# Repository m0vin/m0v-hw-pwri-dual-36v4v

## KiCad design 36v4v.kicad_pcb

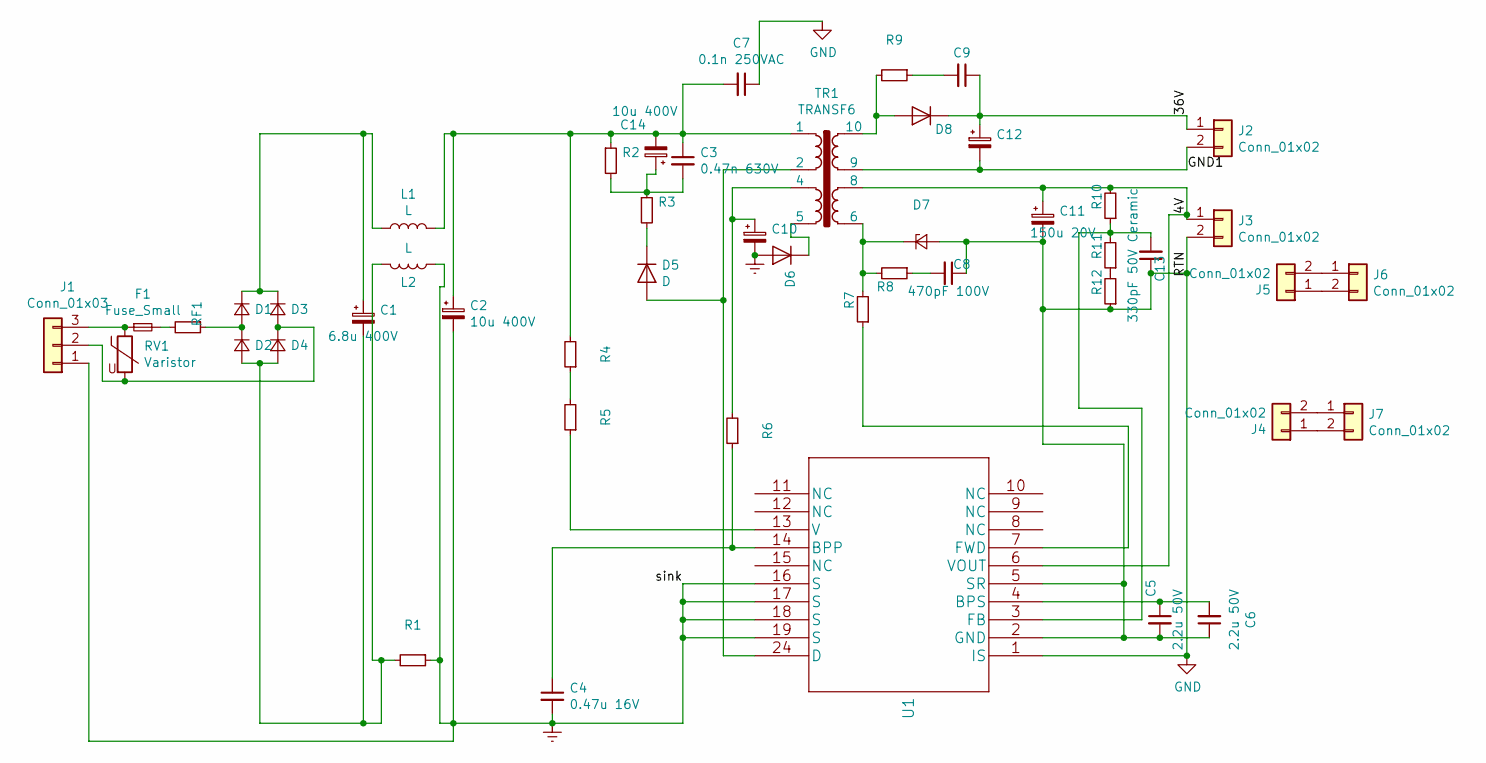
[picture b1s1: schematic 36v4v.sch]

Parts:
C1: 6.8u 400V; CP_Radial_D10.0mm_P5.00mm; MFG Part Num ESH106M450AH4AA/EEV-EB2G100SM
C2, C14: 10u 400V; CP_Radial_D10.0mm_P5.00mm; MFG Part Num ESH106M450AH4AA/EEV-EB2G100SM
C3: 0.47n 630V; CP_Radial_Tantal_D5.5mm_P5.00mm; MFG Part Num RCE7U2J471J2M1H03A
C4: 0.47u 16V; C_0603_1608Metric_Pad1.05x0.95mm_HandSolder; MFG Part Num GRM033R71E471KA01D/FK18X7R1C474K
C5, C6: 2.2u 50V; C_0603_1608Metric_Pad1.05x0.95mm_HandSolder; MFG Part Num GRM188R61H225KE11D/C340C225K5R5TA
C7: 0.1n 250VAC; C_Disc_D8.0mm_W5.0mm_P10.00mm; MFG Part Num 440LT10-R
C8: 470pF 100V; C_0603_1608Metric_Pad1.05x0.95mm_HandSolder; MFG Part Num 885342006005/K471J15C0GH5TH5
C9: 18pF 1KV Ceramic; CP_Radial_D10.0mm_P5.00mm; MFG Part Num ECC-D3A180JGE
C10: 22u 35V Electrolytic; CP_Radial_D5.0mm_P2.00mm; MFG Part Num 860020672011/EEU-FC1V220H
C11: 150u 20V; CP_Radial_D10.0mm_P5.00mm; MFG Part Num PLF1D151MDO2TD/860010674014
C12: 22u 50V Electrolytic; CP_Radial_D5.0mm_P2.00mm; MFG Part Num 860020672011/EKZE500ELL220ME11D
C13: 330pF 50V Ceramic; C_0603_1608Metric_Pad1.05x0.95mm_HandSolder; MFG Part Num 885342006005/K471J15C0GH5TH5
D1, D2, D3, D4: D_Small; D_SMB_Handsoldering; MFG Part Num VS-4EGU06-M3/5BT OR GBL06-E3/45GI-ND OR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
D5: D; D_SMA_Handsoldering; MFG Part Num US1M
D6: 150 V, 0.2 A, Standard Recovery, DO-35; D_SMA_Handsoldering; MFG Part Num US1M/1N3595TR
D7: 40 V, 2 A, Schottky, DO-15; D_SMA_Handsoldering; MFG Part Num B240A-E3/61T OR SB240-E3/54
D8: 400 V, 1 A, Ultrafast Recovery, 30 ns, SOD57; D_SMA_Handsoldering; MFG Part Num US1M/BYV26B-TR
F1: Fuse_Small; Fuseholder_Cylinder-5x20mm_Schurter_0031_8201_Horizontal_Op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
J1: Conn_01x03; PhoenixContact_MCV_1,5_3-G-5.08_1x03_P5.08mm_Vertical
J2, J3, J6, J7: Conn_01x02; PinHeader_1x02_P2.54mm_Vertical
J4, J5: Conn_01x02; SolderWirePad_1x02_P5.08mm_Drill1.5mm
L1, L2: L; L_Radial_D6.0mm_P4.00mm; MFG Part Num SBC2-102-181
R1: 4.7 kΩ, 5 %, 0.25 W, Carbon Film; R_0805_2012Metric_Pad1.15x1.40mm_HandSolder
R2: 240 kΩ, 5 %, 0.25 W, Carbon Film; R_2512_6332Metric_Pad1.52x3.35mm_HandSolder
R3: 43 Ω, 5 %, 0.125 W, Carbon Film; R_0805_2012Metric_Pad1.15x1.40mm_HandSolder
R4, R5: 1.78 MΩ, 1 %, 0.25 W, Metal Film; R_0805_2012Metric_Pad1.15x1.40mm_HandSolder
R6: 14 kΩ, 1 %, 0.125 W, Metal Film; R_0805_2012Metric_Pad1.15x1.40mm_HandSolder
R7: 47 Ω, 5 %, 0.125 W, Carbon Film; R_0603_1608Metric_Pad1.05x0.95mm_HandSolder
R8: 22 Ω, 5 %, 0.25 W, Carbon Film; R_0603_1608Metric_Pad1.05x0.95mm_HandSolder
R9: 560 Ω, 5 %, 0.25 W, Carbon Film; R_0603_1608Metric_Pad1.05x0.95mm_HandSolder
R10: 80.6 kΩ, 1 %, 0.125 W, Metal Film; R_0603_1608Metric_Pad1.05x0.95mm_HandSolder
R11, R12: 29.4 kΩ, 1 %, 0.125 W, Metal Film; R_0603_1608Metric_Pad1.05x0.95mm_HandSolder
RF1: 10 Ω, 2 W, Flameproof Wire-Wound Resistor; R_2816_7142Metric; MFG Part Num SMW210RJT
RV1: Varistor; RV_Disc_D7mm_W4mm_P5mm
TR1: TRANSF6; xformer_2xPri_2xSec
U1: InnoSwitch3-CE, INN3162C, inSOP-24D; INN3162C-H1XX_; MFG Part Num INN3162C-H101

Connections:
/4V: C11.1, J3.1, R10.2, TR1.8, U1.6 (VOUT)
/36V: C9.1, C12.1, D8.1 (K), J2.1
/GND1: C12.2, J2.2, TR1.9
Earth: C2.2, C4.2, C10.2, D6.2 (A), J1.1, L2.1, R1.1, U1.16 (S), U1.17 (S), U1.18 (S), U1.19 (S)
GND: C5.2, C6.1, C7.1, C8.1, C11.2, C13.1, D7.2 (A), J3.2, R12.1, U1.1 (IS), U1.2 (GND), U1.5 (SR)
unnamed: C1.1, D1.1 (K), D3.1 (K), L1.1
unnamed: C1.2, D2.2 (A), D4.2 (A), L2.2, R1.2
unnamed: C4.1, R6.1, U1.14 (BPP)
unnamed: C5.1, C6.2, U1.4 (BPS)
unnamed: C8.2, R8.1
unnamed: C9.2, R9.1
unnamed: C10.1, R6.2, TR1.4
unnamed: C13.2, R10.1, R11.2, U1.3 (FB)
unnamed: C3.2, C14.1, R2.2, R3.1
unnamed: C2.1, C3.1, C7.2, C14.2, L1.2, R2.1, R4.2, TR1.1
unnamed: D1.2 (A), D2.1 (K), RF1.1
unnamed: D3.2 (A), D4.1 (K), J1.2, RV1.2
unnamed: D5.1 (K), R3.2
unnamed: D5.2 (A), TR1.2, U1.24 (D)
unnamed: D6.1 (K), TR1.5
unnamed: D7.1 (K), R7.2, R8.2, TR1.6
unnamed: D8.2 (A), R9.2, TR1.10
unnamed: F1.1, J1.3, RV1.1
unnamed: F1.2, RF1.2
unnamed: J4.1, J7.2
unnamed: J4.2, J7.1
unnamed: J5.1, J6.2
unnamed: J5.2, J6.1
unnamed: R4.1, R5.2
unnamed: R5.1, U1.13 (V)
unnamed: R7.1, U1.7 (FWD)
unnamed: R11.1, R12.2

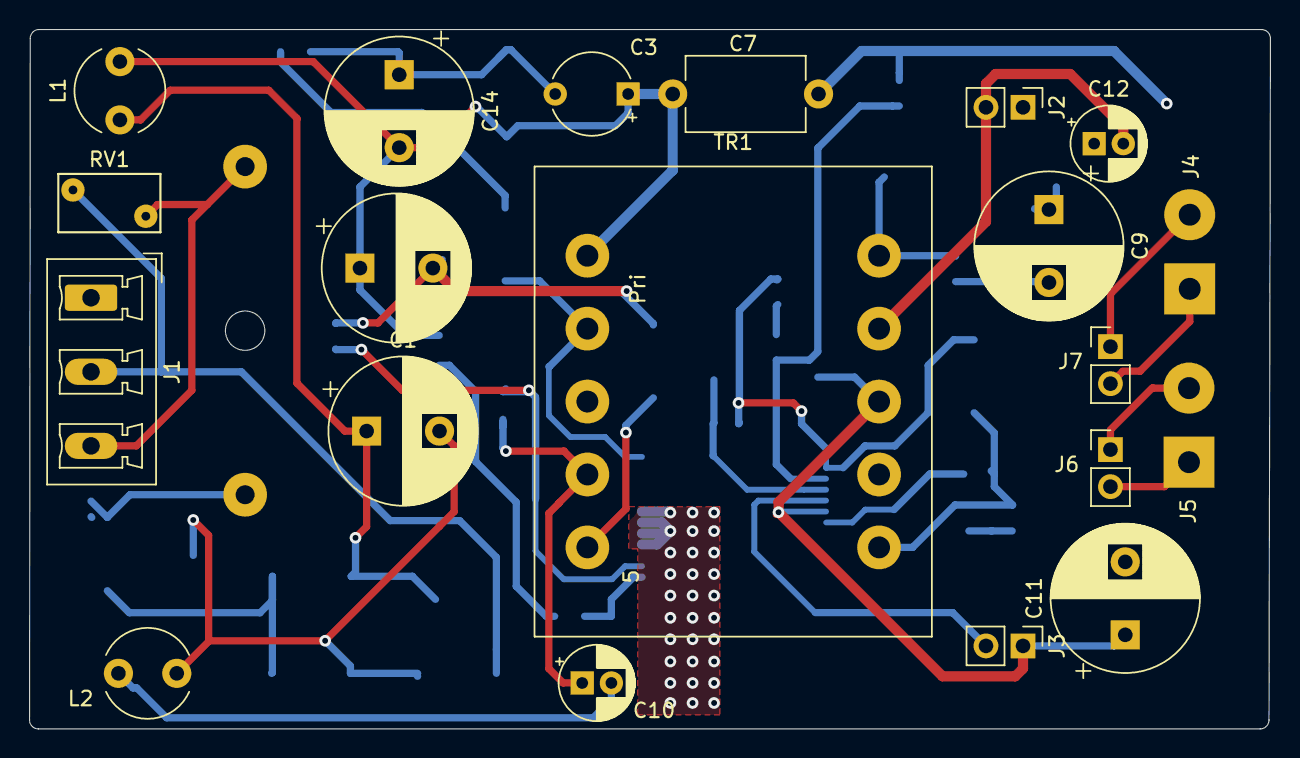
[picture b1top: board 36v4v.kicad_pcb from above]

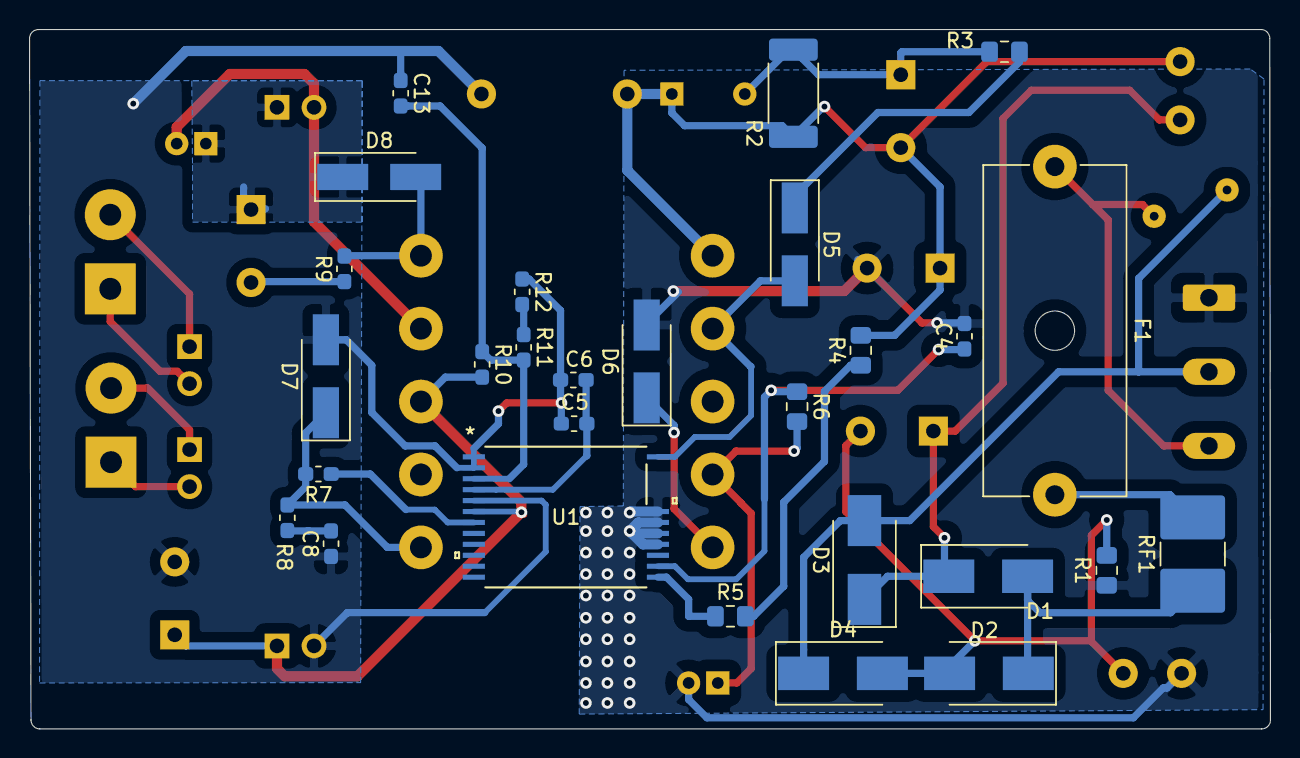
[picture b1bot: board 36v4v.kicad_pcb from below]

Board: 2 copper layers, 85.1 x 48.0 mm, 48 parts (28 on the bottom side), 32 nets.

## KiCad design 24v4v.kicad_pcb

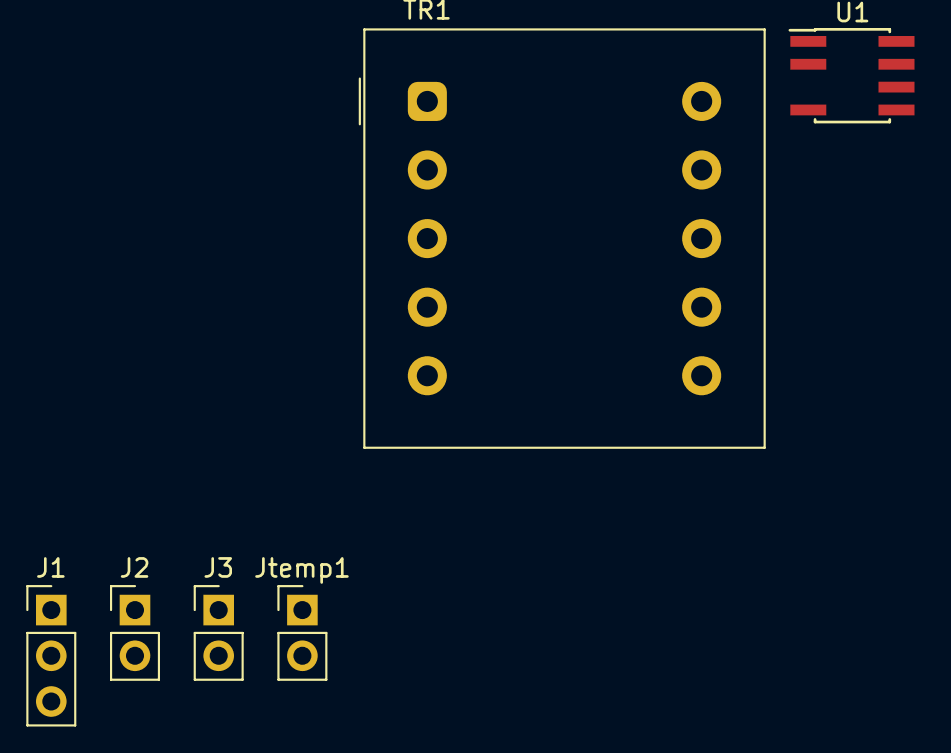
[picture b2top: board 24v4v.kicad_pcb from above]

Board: 2 copper layers, 6 parts (0 on the bottom side), 3 nets, no tracks yet.

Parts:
J1: Conn_01x03; PinHeader_1x03_P2.54mm_Vertical
J2, J3: Conn_01x02; PinHeader_1x02_P2.54mm_Vertical
Jtemp1: Conn_01x02; PinHeader_1x02_P2.54mm_Vertical
TR1: Wuerth_750343373; Transformer_Wuerth_750343373
U1: LNK625DG; PowerIntegrations_SO-8C

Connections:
/GND1: J2.2, TR1.5
unnamed: Jtemp1.1, U1.5, U1.6, U1.7, U1.8
unnamed: TR1.1, U1.4

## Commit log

2020-03-09 Renamed project. Added symbols, footprints for InnoSwitch + xformer
2020-03-23 Incorporated Anil's feedback, BOM
2020-03-30 Changed cap footprints, layout. Added datasheets
2020-04-04 Changed pcz size, modified footprints
2020-04-09 Changes to components and footprints as suggested by AA
2020-04-09 More changes as per AA
2020-04-10 Diode footprint change
2020-04-10 Rotated U1 in schematic to make primary/secondary clearer
2020-04-10 Added 36V zone on back Cu to minimize loop area formed by secondary winding, output rectifier (D8) and output filter cap (C9)
2020-04-10 Y-cap connected directly to DC pin of primary and secondary ground. BYPASS pin cap should be located as close as possible to BYPASS and SOURCE pins
2020-04-10 Maximize hatched area for heat sinking
2020-04-13 Added ground/heatsink for Innoswitch. Added C14 as per Anil

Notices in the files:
parts and their libraries:
Copyright 2016 Accelerated Designs. All rights reserved.
